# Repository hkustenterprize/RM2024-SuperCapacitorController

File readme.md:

# 香港科技大学ENTERPRIZE战队
# RM2024超级电容控制器
# 硬件方案&软件方案 完全开源

>设计者：蒋益诚 戎羿
> 
>文档撰写：戎羿

## 文件结构

```
Calibration/cal.xlsx                              ----校准用Excel工具表
Core                                              ----核心代码文件
Docs                                              ----文档附图源码
Drivers                                           ----STM32驱动文件
hardware                                          ----硬件项目文件
      --    SuperCap2024_Control_V1.1R_F3_ISOPWR  ----控制板Kicad项目文件
      --    SuperCap2024_Power_V1.2R              ----功率板Kicad项目文件
Middlewares/ST/ARM/DSP/Inc/arm_math.h             ----数学加速库头文件
.clang-format
.clang-tidy
.cproject
CMakeLists.txt                                    ----由CLion生成的CMake编译文件，便于CLion创建项目
CMakeLists_template.txt
Makefile                                          ----由CubeMX生成的MakeFile编译文件
RM2024-SuperCap-F3-V0.2.ioc                       ----STM32CubeMX项目文件
startup_stm32f334x8.s                             ----由CubeMX生成的启动文件
startup_stm32f334x8_SuperCap.s                    ----由CubeMX生成的启动文件改版，当前使用中
STM32F334R8Tx_FLASH.ld                            ----由CubeMX生成的链接文件
STM32F334R8Tx_SuperCap_FLASH.ld                   ----由CubeMX生成的链接文件改版，当前使用中
SuperCap-F3.mk                                    ----队内通用MakeFile库
```

## 使用方法
###	硬件接口&连接

###	软件环境&编译&烧录
本项目基于GCC ARM GNU工具链。
1.	安装GCC环境。以Windows系统下为例，下载MSYS2并安装，在系统环境变量中加入相关目录。
2.	安装`arm-none-eabi-gcc`
      然后即可执行编译操作。需要注意编译时需要指定HARDWARE_ID，否则将会报错。

      `make -j HARDWARE_ID=xxx`

      得到`build/`目录下`RM2024-SuperCap-F3-V1R.elf`文件即为编译成功。

      将elf文件在ozone新建项目中打开，即可通过JLink烧录至MCU中。

## 移植兼容性
该项目通过STM32的HAL库实现大部分去耦，方便移植。

用户代码全部位于 `Core/` 中，将相应文件转移到另生成的项目中可以轻松移植。例如专用STM32G474作为开发用MCU。

而部分相对底层的外设代码，例如HRTIM与ADC的配置等，则需要手动修改。

总体而言该项目可移植性较佳。

## 开源报告
可以见于Github Release处

## 开源说明
本项目通过GPL3.0协议开源

## PCB项目说明
硬件部分使用KiCAD设计。

Github上在线预览：使用[KiCanvas](https://kicanvas.org/)

上板原理图：[预览](https://kicanvas.org/?github=https%3A%2F%2Fgithub.com%2Fhkustenterprize%2FRM2024-SuperCapacitorController%2Fblob%2Fmaster%2Fhardware%2FSuperCap2024_Control_V1.1R_F3_ISOPWR%2FSuperCap2024Control_V1.1R_F3_ISOPWR.kicad_sch)

上板PCB：[预览](https://kicanvas.org/?github=https%3A%2F%2Fgithub.com%2Fhkustenterprize%2FRM2024-SuperCapacitorController%2Fblob%2Fmaster%2Fhardware%2FSuperCap2024_Control_V1.1R_F3_ISOPWR%2FSuperCap2024Control_V1.1R_F3_ISOPWR.kicad_pcb)

下板原理图：[预览](https://kicanvas.org/?github=https%3A%2F%2Fgithub.com%2Fhkustenterprize%2FRM2024-SuperCapacitorController%2Fblob%2Fmaster%2Fhardware%2FSuperCap2024_Power_V1.2R%2FSuperCap2024V1.2R_Power.kicad_sch)

下板PCB：[预览](https://kicanvas.org/?github=https%3A%2F%2Fgithub.com%2Fhkustenterprize%2FRM2024-SuperCapacitorController%2Fblob%2Fmaster%2Fhardware%2FSuperCap2024_Power_V1.2R%2FSuperCap2024V1.2R_Power.kicad_pcb)

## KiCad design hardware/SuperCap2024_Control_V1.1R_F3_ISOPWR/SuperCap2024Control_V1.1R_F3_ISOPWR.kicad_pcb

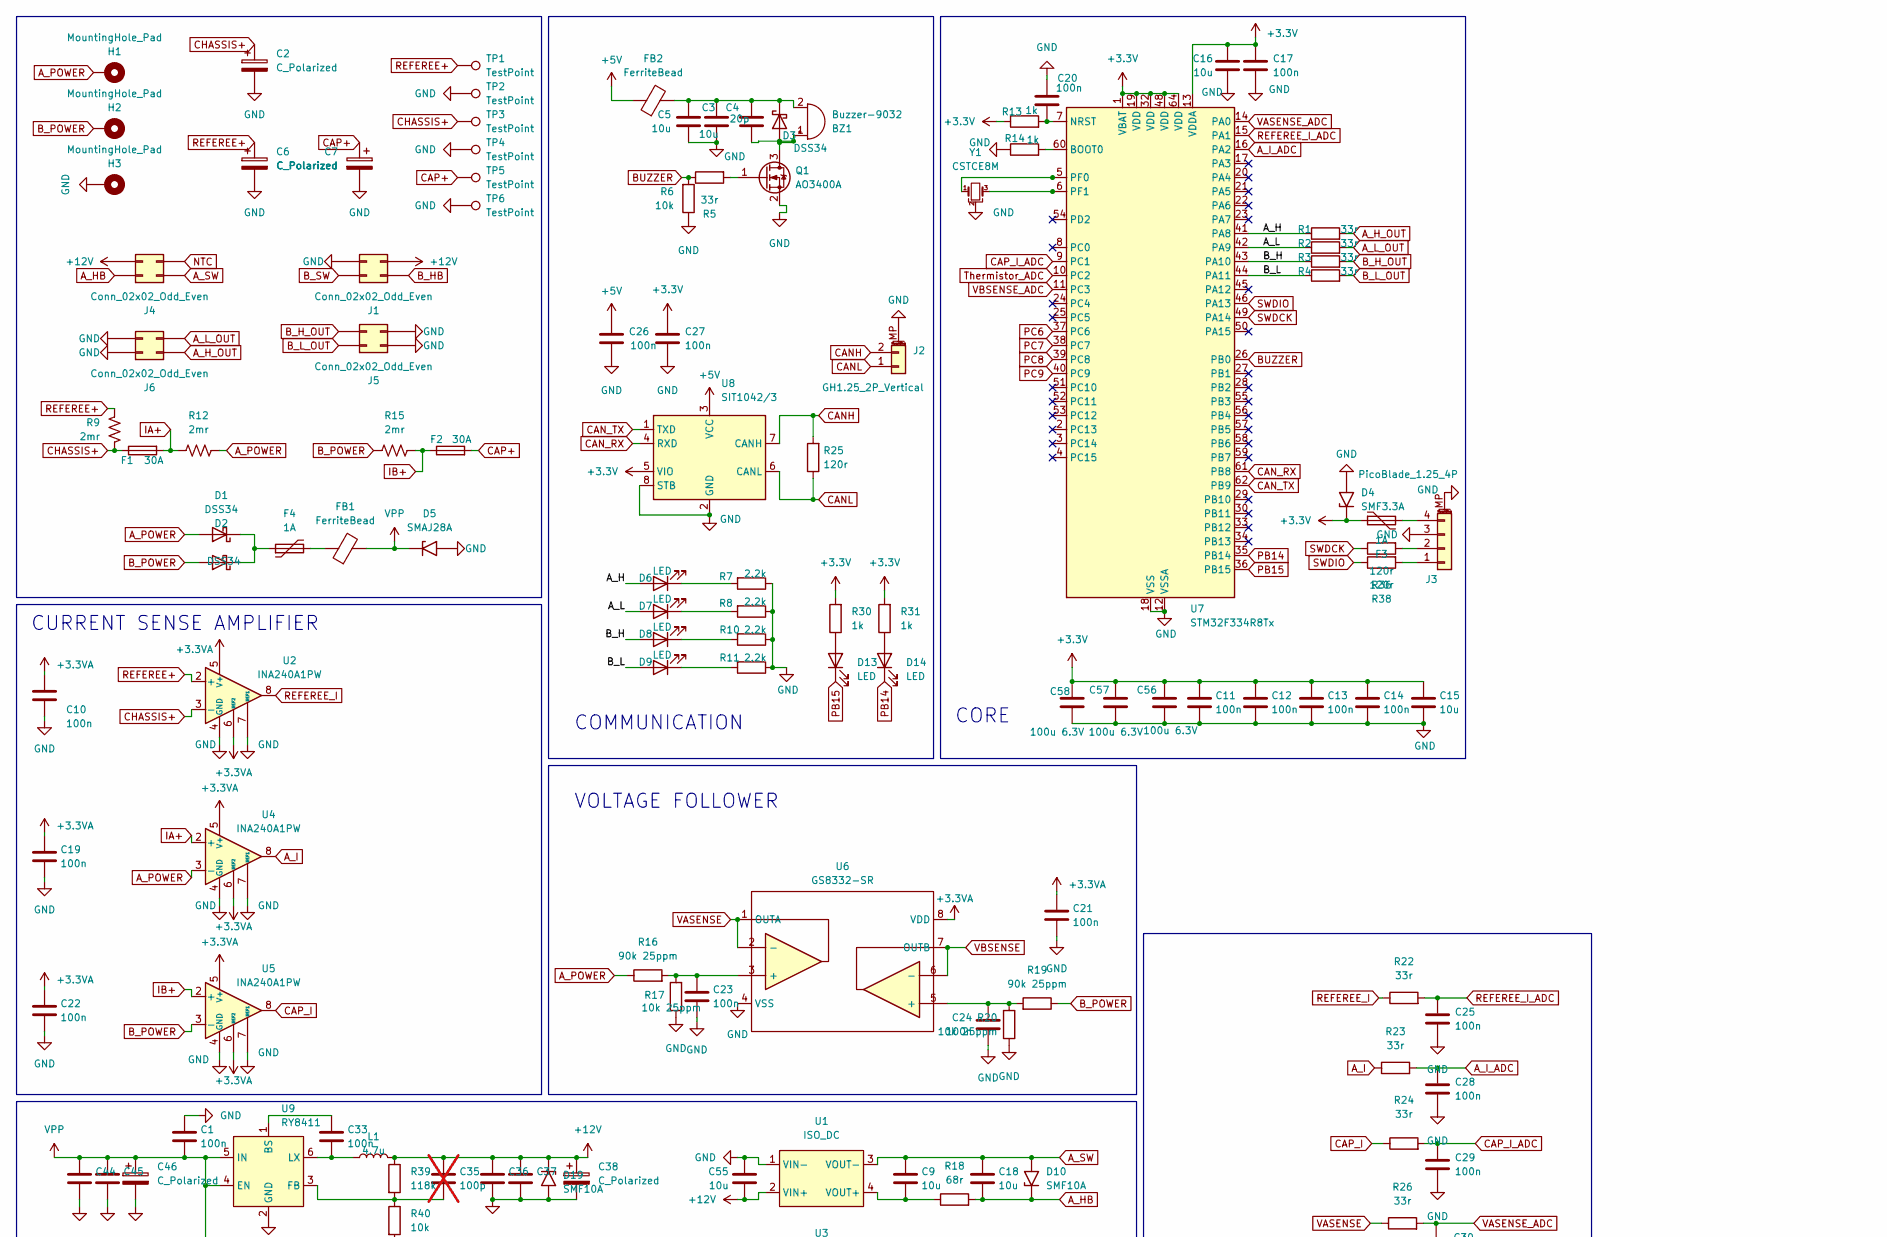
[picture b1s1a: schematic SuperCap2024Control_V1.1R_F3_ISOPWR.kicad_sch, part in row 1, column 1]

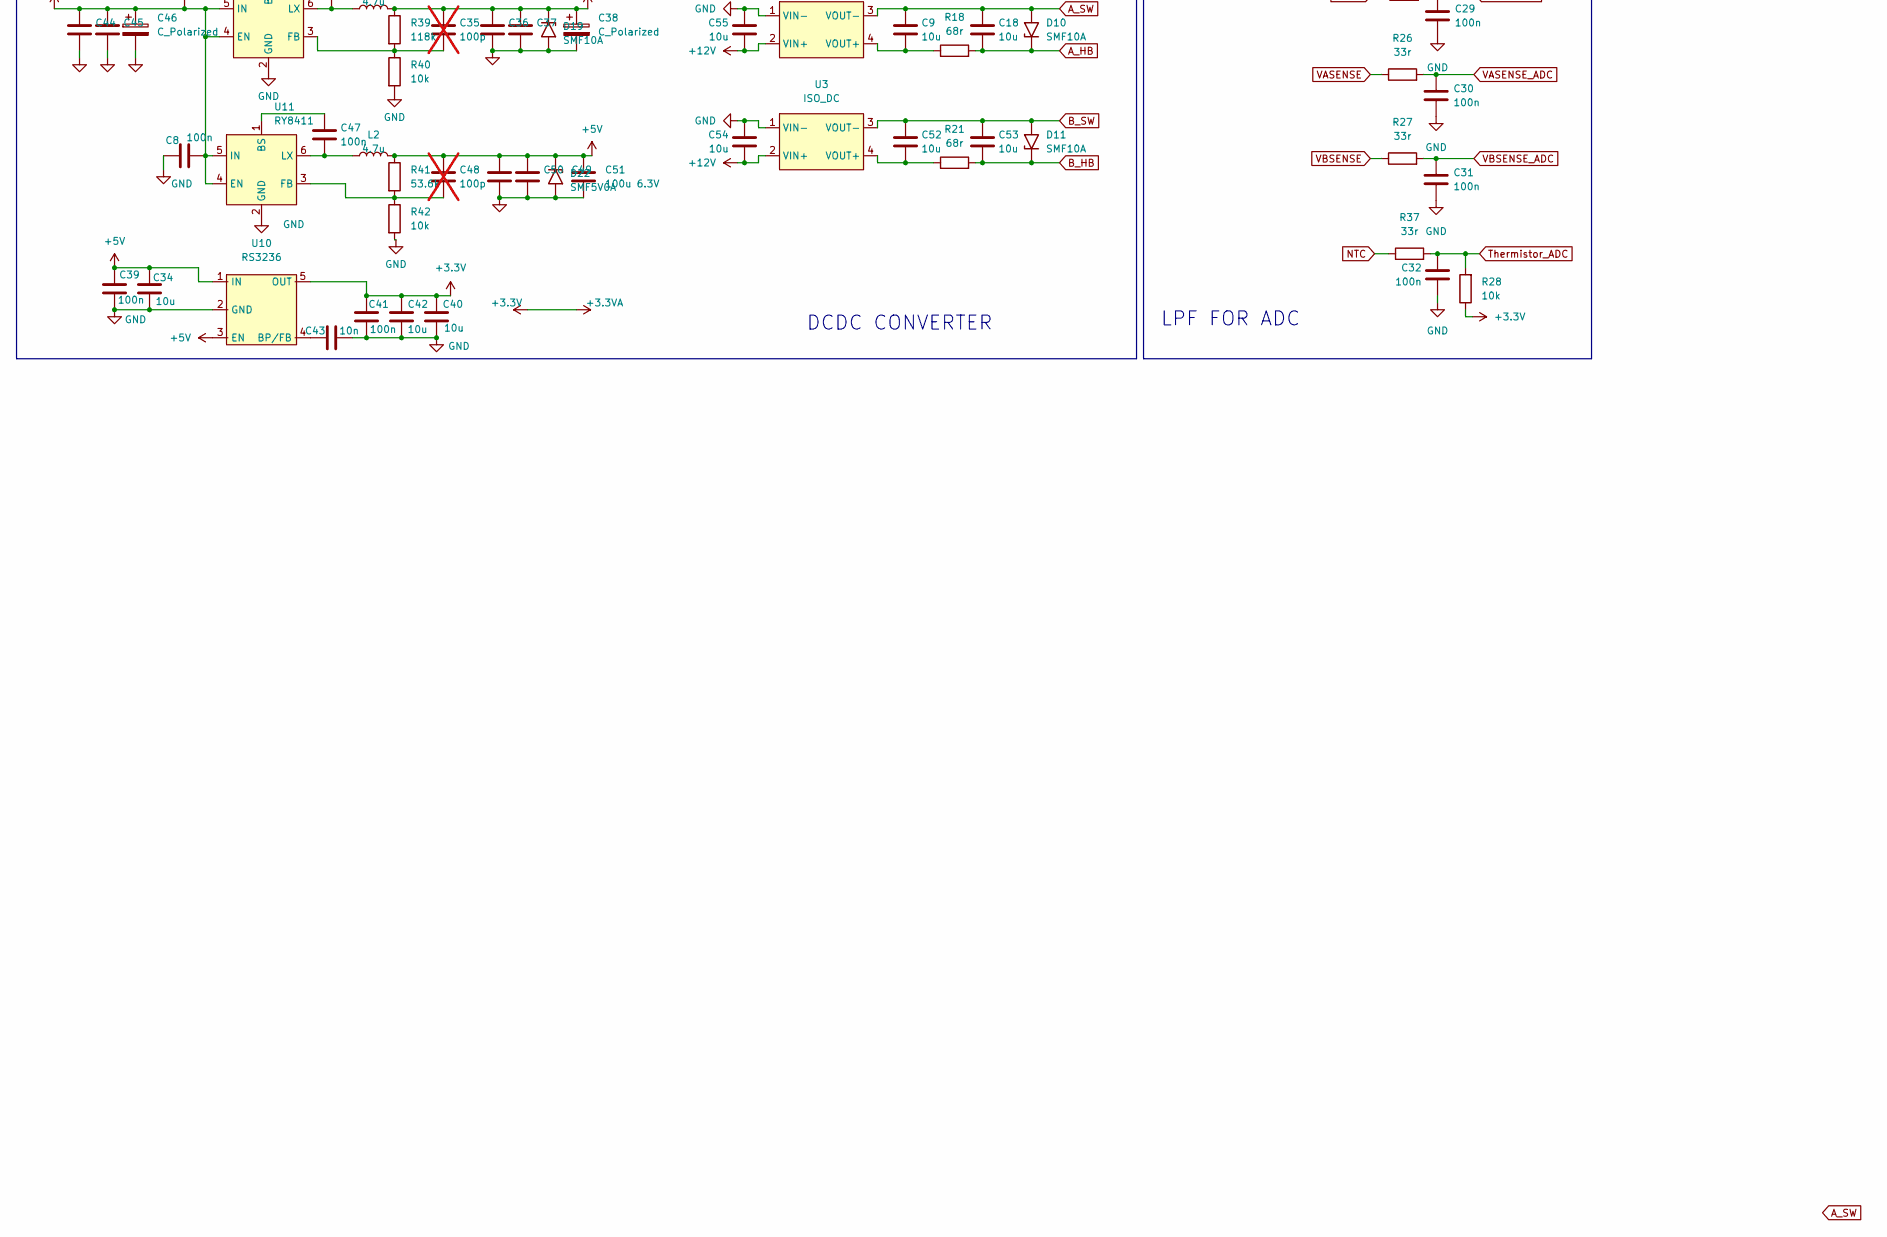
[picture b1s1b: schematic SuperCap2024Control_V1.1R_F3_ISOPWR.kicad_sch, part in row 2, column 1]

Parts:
BZ1: Buzzer-9032; MLT-9032
C1, C8, C10, C11, C12, C13, C14, C17, C19, C20, C21, C22, C23, C24, C25, C26, C27, C28, C29, C30, C31, C32, C33, C39, C41, C47: 100n; C_0603_1608Metric
C2, C6, C7: C_Polarized; CP_Radial_D8.0mm_P3.50mm
C3, C5, C15, C16, C34, C40, C42: 10u; C_0603_1608Metric
C4: 20p; C_0603_1608Metric
C9, C18, C36, C37, C44, C45, C49, C50, C52, C53, C54, C55: 10u; C_1206_3216Metric
C35, C48: 100p; C_0603_1608Metric; not fitted
C38, C46: C_Polarized; CP_EIA-6032-28_Kemet-C
C43: 10n; C_0603_1608Metric
C51, C56, C57, C58: 100u 6.3V; C_1206_3216Metric
D1, D2, D3: DSS34; D_SMF
D4: SMF3.3A; D_SMF
D5: SMAJ28A; D_SMA
D6, D7, D8, D9, D13, D14: LED; LED_0603_1608Metric
D10, D11, D19: SMF10A; D_SMF
D22: SMF5V0A; D_SMF
F1, F2: 30A; Fuse_1206_3216Metric
F3, F4: 1A; Fuse_1206_3216Metric
FB1: FerriteBead; L_1206_3216Metric
FB2: FerriteBead; L_0603_1608Metric
H1, H2, H3: MountingHole_Pad; MountingHole_3.2mm_M3_ISO14580_Pad
J1, J4: Conn_02x02_Odd_Even; PinHeader_2x02_P2.54mm_Vertical_SMD
J2: GH1.25_2P_Vertical; JST_GH_SM02B-GHS-TB_1x02-1MP_P1.25mm_Horizontal
J3: PicoBlade_1.25_4P; Molex_PicoBlade_53261-0471_1x04-1MP_P1.25mm_Horizontal
J5, J6: Conn_02x02_Odd_Even; PinHeader_2x02_P2.54mm_Vertical
L1: 4.7u; L_Bourns-SRN4018
L2: 4.7u; L_Sunlord_SWPA252012S
Q1: AO3400A; SOT-23
R1, R2, R3, R4, R5, R22, R23, R24, R26, R27, R37: 33r; R_0603_1608Metric
R6, R28, R40, R42: 10k; R_0603_1608Metric
R7, R8, R10, R11: 2.2k; R_0603_1608Metric
R9, R12, R15: 2mr; R_2512_6332Metric
R13, R14, R30, R31: 1k; R_0603_1608Metric
R16, R19: 90k 25ppm; R_0603_1608Metric
R17, R20: 10k 25ppm; R_0603_1608Metric
R18, R21: 68r; R_0603_1608Metric
R25, R36, R38: 120r; R_0603_1608Metric
R39: 118k; R_0603_1608Metric
R41: 53.6k; R_0603_1608Metric
TP1, TP2, TP3, TP4, TP5, TP6: TestPoint; TestPoint_Plated_Hole_D3.0mm
U1, U3: ISO_DC; BxxxxS-1W
U2, U4, U5: INA240A1PW; TSSOP-8_4.4x3mm_P0.65mm
U6: GS8332-SR; SOIC-8_3.9x4.9mm_P1.27mm
U7: STM32F334R8Tx; LQFP-64_10x10mm_P0.5mm
U8: SIT1042/3; SOIC-8_3.9x4.9mm_P1.27mm
U9, U11: RY8411; SOT-23-6
U10: RS3236; SOT-23-5
Y1: CSTCE8M; Resonator_SMD_Murata_CSTxExxV-3Pin_3.0x1.1mm

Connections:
+3.3V: C10.1, C11.1, C12.1, C13.1, C14.1, C15.1, C16.2, C17.2, C19.1, C21.1, C22.1, C27.2, C40.1, C41.1, C42.1, C56.1, C57.1, C58.1, D4.1 (A1), F3.1, R13.1, R28.1, R30.2, R31.2, U2.5 (V+), U2.6 (REF2), U4.5 (V+), U4.6 (REF2), U5.5 (V+), U5.6 (REF2), U6.8 (VDD), U7.1 (VBAT), U7.13 (VDDA), U7.19 (VDD), U7.32 (VDD), U7.48 (VDD), U7.64 (VDD), U8.5 (VIO), U10.5 (OUT)
+5V: C26.2, C34.1, C39.1, C48.1, C49.1, C50.1, C51.1, D22.1 (A1), FB2.1, L2.2, R41.1, U8.3 (VCC), U10.1 (IN), U10.3 (EN)
+12V: C35.1, C36.1, C37.1, C38.1, C54.2, C55.2, D19.1 (A1), J1.4, J4.3, L1.2, R39.1, U1.2 (VIN+), U3.2 (VIN+)
/A_H: D6.2 (A), R1.1, U7.41 (PA8)
/A_L: D7.2 (A), R2.1, U7.42 (PA9)
/B_H: D8.2 (A), R3.1, U7.43 (PA10)
/B_L: D9.2 (A), R4.1, U7.44 (PA11)
A_HB: C18.2, D10.1 (A1), J4.1, R18.2
A_H_OUT: J6.2, R1.2
A_I: R23.1, U4.8
A_I_ADC: C28.2, R23.2, U7.16 (PA2)
A_L_OUT: J6.4, R2.2
A_POWER: D1.2 (A), H1.1, R12.2, R16.1, U4.3 (-)
A_SW: C9.1, C18.1, D10.2 (A2), J4.2, U1.3 (VOUT-)
BUZZER: R5.1, R6.2, U7.26 (PB0)
B_HB: C53.2, D11.1 (A1), J1.2, R21.2
B_H_OUT: J5.3, R3.2
B_L_OUT: J5.1, R4.2
B_POWER: D2.2 (A), H2.1, R15.1, R19.1, U5.3 (-)
B_SW: C52.1, C53.1, D11.2 (A2), J1.1, U3.3 (VOUT-)
CANH: J2.2, R25.2, U8.7 (CANH)
CANL: J2.1, R25.1, U8.6 (CANL)
CAN_RX: U7.61 (PB8), U8.4 (RXD)
CAN_TX: U7.62 (PB9), U8.1 (TXD)
CAP+: C7.1, F2.2, TP5.1
CAP_I: R24.1, U5.8
CAP_I_ADC: C29.2, R24.2, U7.9 (PC1)
CHASSIS+: C2.1, F1.1, R9.2, TP3.1, U2.3 (-)
GND: C1.1, C2.2, C3.1, C5.1, C6.2, C7.2, C8.2, C10.2, C11.2, C12.2, C13.2, C14.2, C15.2, C16.1, C17.1, C19.2, C20.2, C21.2, C22.2, C23.2, C24.2, C25.1, C26.1, C27.1, C28.1, C29.1, C30.1, C31.1, C32.2, C34.2, C36.2, C37.2, C38.2, C39.2, C40.2, C41.2, C42.2, C43.2, C44.2, C45.2, C46.2, C49.2, C50.2, C51.2, C54.1, C55.1, C56.2, C57.2, C58.2, D4.2 (A2), D5.2 (A2), D19.2 (A2), D22.2 (A2), H3.1, J1.3, J2.MP (MountPin), J3.3, J3.MP (MountPin), J5.2, J5.4, J6.1, J6.3, Q1.2 (S), R6.1, R7.1, R8.1, R10.1, R11.1, R14.1, R17.1, R20.1, R40.2, R42.2, TP2.1, TP4.1, TP6.1, U1.1 (VIN-), U2.1 (GND), U2.4 (GND), U2.7 (REF1), U3.1 (VIN-), U4.1 (GND), U4.4 (GND), U4.7 (REF1), U5.1 (GND), U5.4 (GND), U5.7 (REF1), U6.4 (VSS), U7.12 (VSSA), U7.18 (VSS), U7.31 (VSS), U7.47 (VSS), U7.63 (VSS), U8.2 (GND), U8.8 (STB), U9.2 (GND), U10.2 (GND), U11.2 (GND), Y1.2
IA+: F1.2, R12.1, U4.2 (+)
IB+: F2.1, R15.2, U5.2 (+)
NTC: J4.4, R37.1
unnamed: BZ1.2 (+), C3.2, C4.2, C5.2, D3.1 (K), FB2.2
unnamed: BZ1.1 (-), C4.1, D3.2 (A), Q1.3 (D)
unnamed: C23.1, R16.2, R17.2, U6.3 (+)
unnamed: C24.1, R19.2, R20.2, U6.5 (+)
unnamed: D1.1 (K), D2.1 (K), F4.1
unnamed: D6.1 (K), R7.2
unnamed: D7.1 (K), R8.2
unnamed: D8.1 (K), R10.2
unnamed: D9.1 (K), R11.2
unnamed: D13.2 (A), R30.1
unnamed: D14.2 (A), R31.1
unnamed: F4.2, FB1.1
unnamed: J3.1, R38.2
unnamed: J3.2, R36.2
unnamed: F3.2, J3.4
unnamed: Q1.1 (G), R5.2
unnamed: C9.2, R18.1, U1.4 (VOUT+)
unnamed: C52.2, R21.1, U3.4 (VOUT+)
unnamed: R14.2, U7.60 (BOOT0)
unnamed: C20.1, R13.2, U7.7 (NRST)
unnamed: U7.5 (PF0), Y1.1
unnamed: U7.6 (PF1), Y1.3
unnamed: C33.1, U9.1 (BS)
unnamed: C35.2, R39.2, R40.1, U9.3 (FB)
unnamed: C33.2, L1.1, U9.6 (LX)
unnamed: C43.1, U10.4 (BP/FB)
unnamed: C47.1, U11.1 (BS)
unnamed: C48.2, R41.2, R42.1, U11.3 (FB)
unnamed: C47.2, L2.1, U11.6 (LX)
PB14: D14.1 (K), U7.35 (PB14)
PB15: D13.1 (K), U7.36 (PB15)
PC6: U7.37 (PC6)
PC7: U7.38 (PC7)
PC8: U7.39 (PC8)
PC9: U7.40 (PC9)
REFEREE+: C6.1, R9.1, TP1.1, U2.2 (+)
REFEREE_I: R22.1, U2.8
REFEREE_I_ADC: C25.2, R22.2, U7.15 (PA1)
SWDCK: R36.1, U7.49 (PA14)
SWDIO: R38.1, U7.46 (PA13)
Thermistor_ADC: C32.1, R28.2, R37.2, U7.10 (PC2)
VASENSE: R26.1, U6.1 (OUTA), U6.2 (-)
VASENSE_ADC: C30.2, R26.2, U7.14 (PA0)
VBSENSE: R27.1, U6.6 (-), U6.7 (OUTB)
VBSENSE_ADC: C31.2, R27.2, U7.11 (PC3)
VPP: C1.2, C8.1, C44.1, C45.1, C46.1, D5.1 (A1), FB1.2, U9.4 (EN), U9.5 (IN), U11.4 (EN), U11.5 (IN)

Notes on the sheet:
COMMUNICATION
CURRENT SENSE AMPLIFIER
CORE
DCDC CONVERTER
VOLTAGE FOLLOWER
LPF FOR ADC

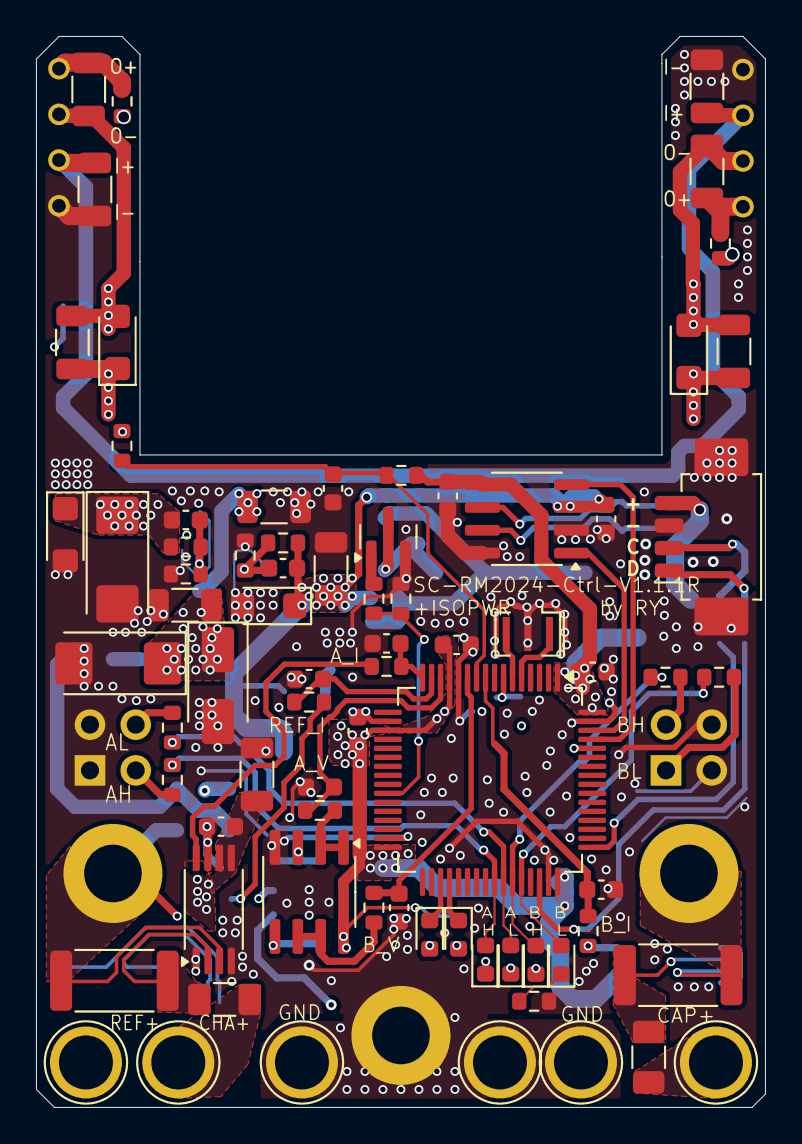
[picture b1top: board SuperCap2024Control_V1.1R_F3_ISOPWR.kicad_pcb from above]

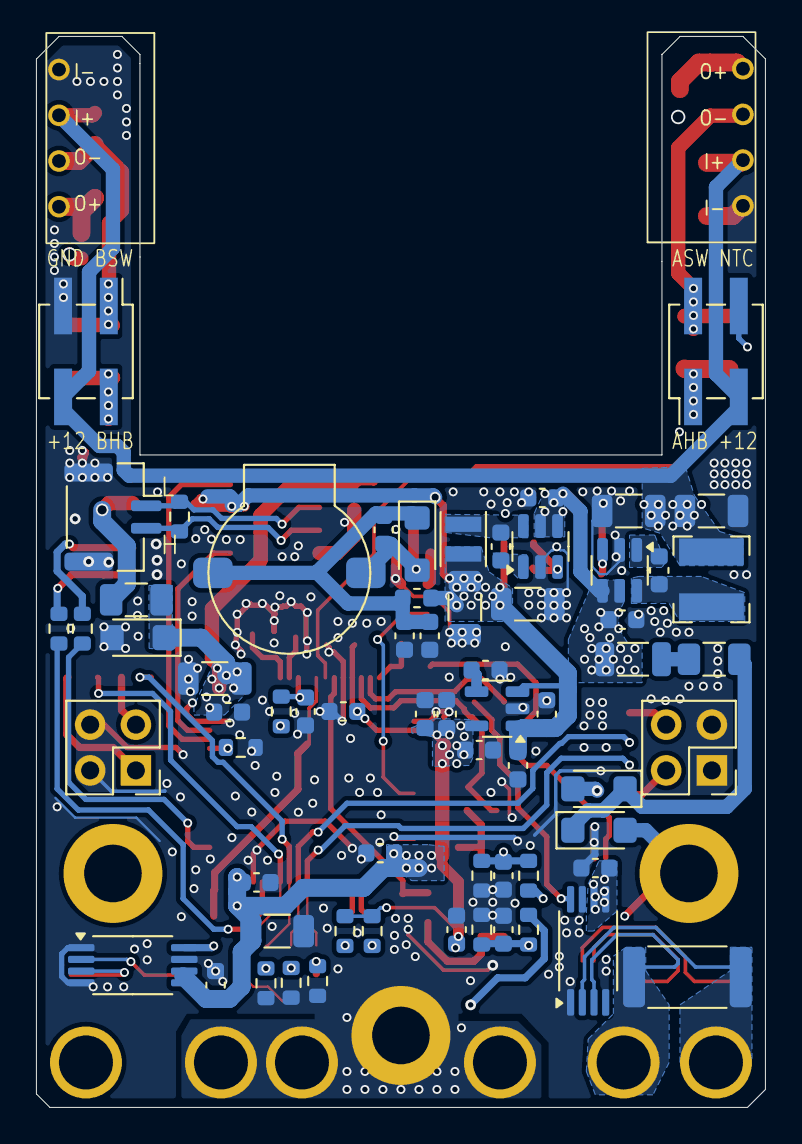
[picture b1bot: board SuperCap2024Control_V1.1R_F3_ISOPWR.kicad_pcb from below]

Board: 4 copper layers, 40.5 x 59.5 mm, 144 parts (67 on the bottom side), 74 nets.

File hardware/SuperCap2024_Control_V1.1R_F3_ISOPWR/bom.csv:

Designator,Footprint,Quantity,Value,LCSC Part #
BZ1,MLT-9032,1,Buzzer-9032,
"C1, C10, C11, C12, C13, C14, C17, C19, C20, C21, C22, C23, C24, C25, C26, C27, C28, C29, C30, C31, C32, C33, C39, C41, C47, C8",0603,26,100n,
"C15, C16, C3, C34, C40, C42, C5",0603,7,10u,
"C18, C36, C37, C44, C45, C49, C50, C52, C53, C54, C55, C9",1206,12,10u,
"C38, C46",CP_EIA-6032-28_Kemet-C,2,C_Polarized,
C4,0603,1,20p,
C43,0603,1,10n,
"C51, C56, C57, C58",1206,4,100u 6.3V,
"D1, D2, D3",D_SMF,3,DSS34,
"D10, D11, D19",D_SMF,3,SMF10A,
"D13, D14, D6, D7, D8, D9",0603,6,LED,
D22,D_SMF,1,SMF5V0A,
D4,D_SMF,1,SMF3.3A,
D5,D_SMA,1,SMAJ28A,
"F1, F2",1206,2,30A,
"F3, F4",1206,2,1A,
FB1,1206,1,FerriteBead,
FB2,0603,1,FerriteBead,
"H1, H2, H3",MountingHole_3.2mm_M3_ISO14580_Pad,3,MountingHole_Pad,
"J1, J4",PinHeader_2x02_P2.54mm_Vertical_SMD,2,Conn_02x02_Odd_Even,
J2,JST_GH_SM02B-GHS-TB_1x02-1MP_P1.25mm_Horizontal,1,Conn_01x02_MountingPin,
J3,Molex_PicoBlade_53261-0471_1x04-1MP_P1.25mm_Horizontal,1,Conn_01x04_MountingPin,
"J5, J6",PinHeader_2x02_P2.54mm_Vertical,2,Conn_02x02_Odd_Even,
L1,L_Bourns-SRN4018,1,4.7u,
L2,L_Sunlord_SWPA252012S,1,4.7u,
Q1,SOT-23,1,AO3400A,
"R1, R2, R22, R23, R24, R26, R27, R3, R37, R4, R5",0603,11,33r,
"R10, R11, R7, R8",0603,4,2.2k,
"R12, R15, R9",2512,3,2mr,
"R13, R14, R30, R31",0603,4,1k,
"R16, R19",0603,2,90k 25ppm,
"R17, R20",0603,2,10k 25ppm,
"R18, R21",0603,2,68r,
"R25, R36, R38",0603,3,120r,
"R28, R40, R42, R6",0603,4,10k,
R39,0603,1,118k,
R41,0603,1,53.6k,
"TP1, TP2, TP3, TP4, TP5, TP6",TestPoint_Plated_Hole_D3.0mm,6,TestPoint,
"U1, U3",BxxxxS-1W,2,ISO_DC,
U10,SOT-23-5,1,RS3236,
"U11, U9",SOT-23-6,2,RY8411,
"U2, U4, U5",TSSOP-8_4.4x3mm_P0.65mm,3,INA240A1PW,
U6,SOIC-8_3.9x4.9mm_P1.27mm,1,GS8332-SR,
U7,LQFP-64_10x10mm_P0.5mm,1,STM32F334R8Tx,
U8,SOIC-8_3.9x4.9mm_P1.27mm,1,SIT1042/3,
Y1,Resonator_SMD_Murata_CSTxExxV-3Pin_3.0x1.1mm,1,CSTCE8M,

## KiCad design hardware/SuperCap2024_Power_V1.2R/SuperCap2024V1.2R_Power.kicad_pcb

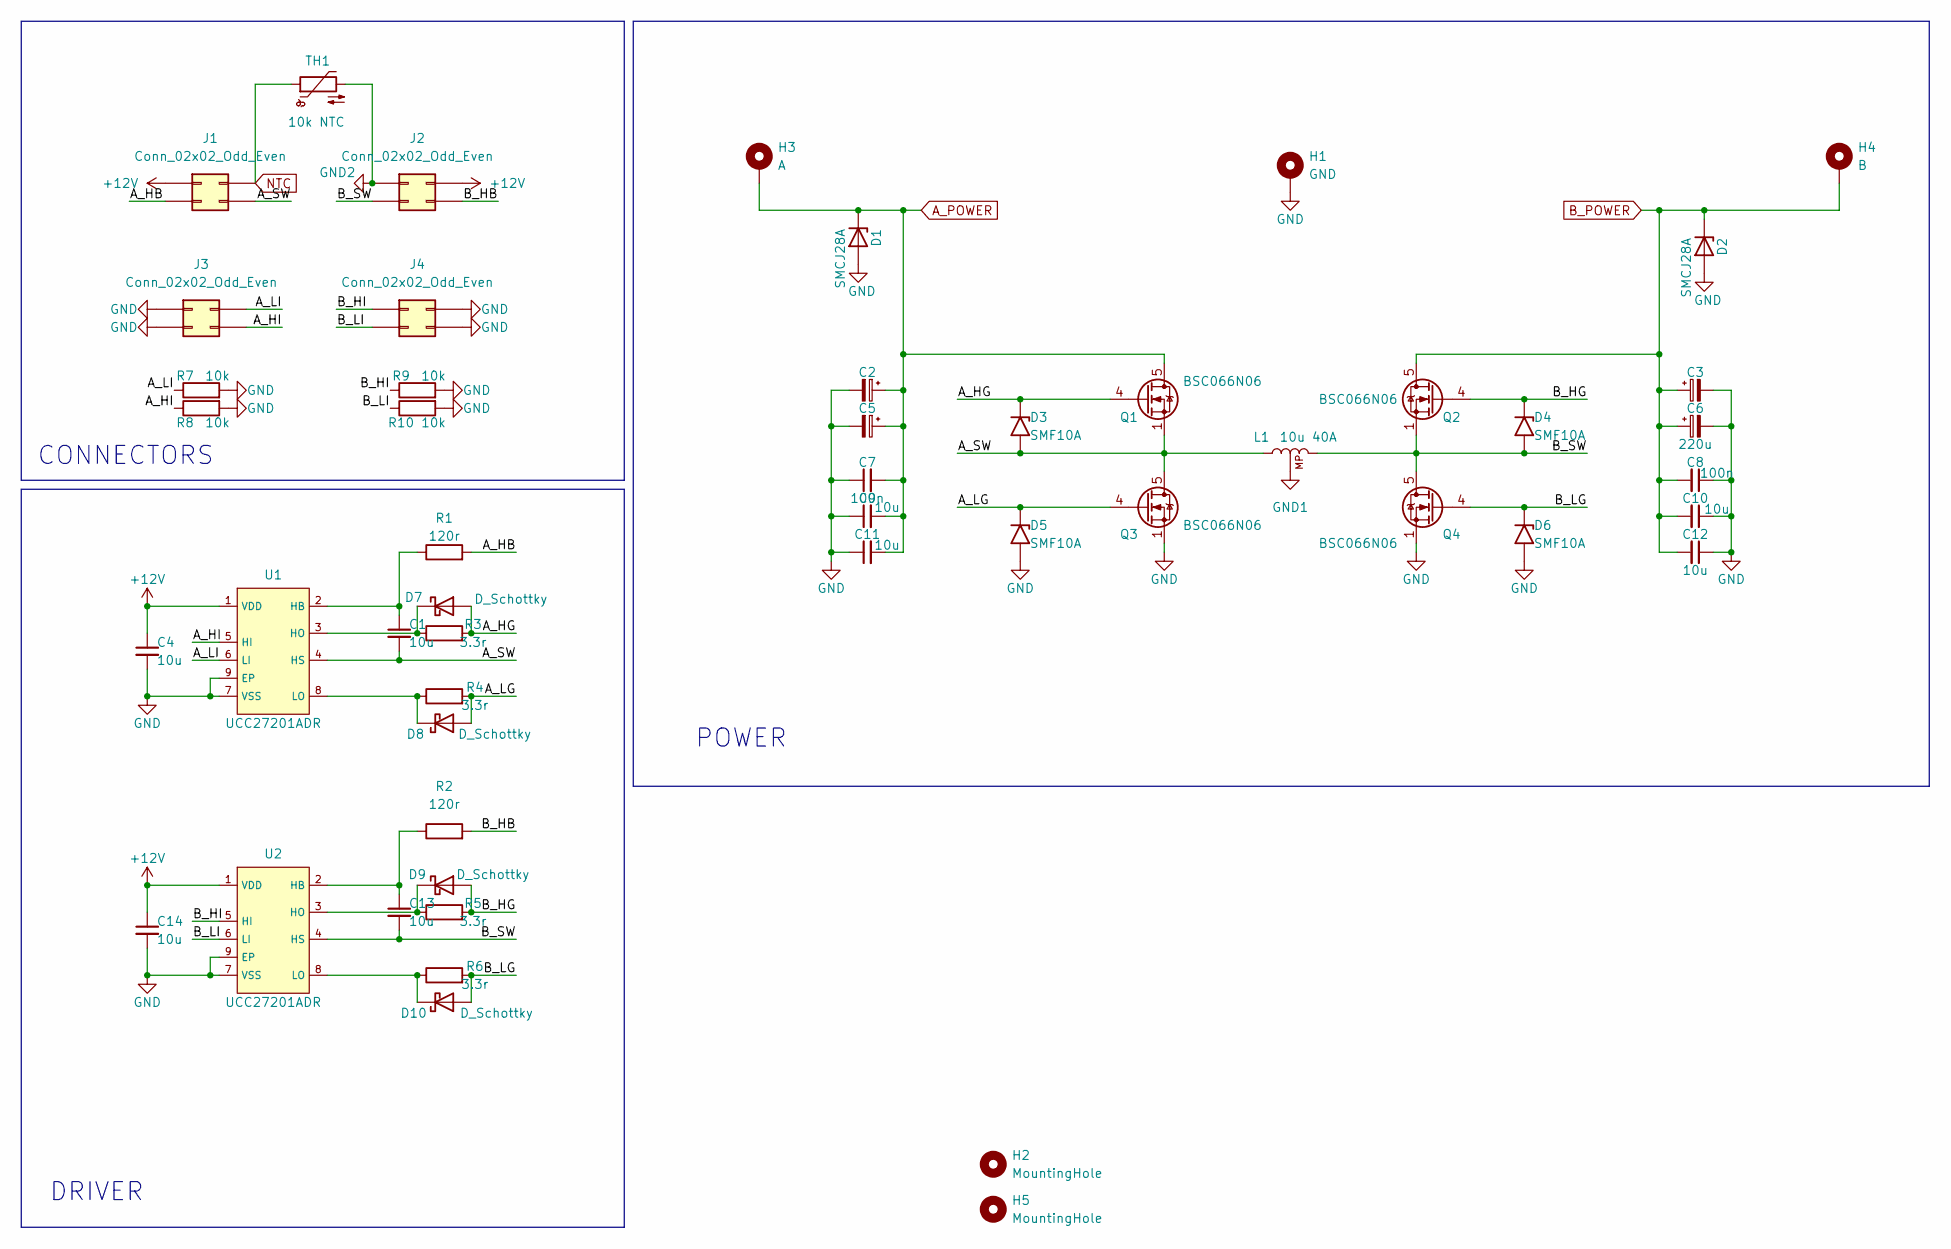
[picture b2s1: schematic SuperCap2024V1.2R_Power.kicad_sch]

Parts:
C1, C13: 10u; C_0603_1608Metric
C2, C3, C5, C6: 220u; CP_Elec_8x10
C4, C9, C10, C11, C12, C14: 10u; C_1206_3216Metric
C7, C8: 100n; C_0603_1608Metric
D1, D2: SMCJ28A; D_SMC
D3, D4, D5, D6: SMF10A; D_SOD-123F
D7, D8, D9, D10: D_Schottky; D_SOD-123F
H1: GND; TestPoint_Pad_D4.0mm
H2, H5: MountingHole; MountingHole_3.2mm_M3
H3: A; TestPoint_Pad_D4.0mm
H4: B; TestPoint_Pad_D4.0mm
J1, J2, J3, J4: Conn_02x02_Odd_Even; PinHeader_2x02_P2.54mm_Vertical_SMD
L1: 10u 40A; PQ2617BHA
Q1, Q2, Q3, Q4: BSC066N06; TDSON-8-1_HandSolder
R1, R2: 120r; R_1206_3216Metric
R3, R4, R5, R6: 3.3r; R_0603_1608Metric
R7, R8, R9, R10: 10k; R_0603_1608Metric
TH1: 10k NTC; R_1206_3216Metric
U1, U2: UCC27201ADR; SOP-8_3.9x4.9mm_P1.27mm

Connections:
+12V: C4.1, C14.1, J1.1, J2.2, U1.1 (VDD), U2.1 (VDD)
/A_HB: J1.3, R1.2
/A_HG: D3.1 (A1), D7.2 (A), Q1.4 (G), R3.2
/A_HI: J3.4, R8.1, U1.5 (HI)
/A_LG: D5.1 (A1), D8.2 (A), Q3.4 (G), R4.2
/A_LI: J3.2, R7.1, U1.6 (LI)
/A_SW: C1.2, D3.2 (A2), J1.4, L1.1, Q1.1 (S), Q1.2 (S), Q1.3 (S), Q3.5 (D), U1.4 (HS)
/B_HB: J2.4, R2.2
/B_HG: D4.1 (A1), D9.2 (A), Q2.4 (G), R5.2
/B_HI: J4.1, R9.1, U2.5 (HI)
/B_LG: D6.1 (A1), D10.2 (A), Q4.4 (G), R6.2
/B_LI: J4.3, R10.1, U2.6 (LI)
/B_SW: C13.2, D4.2 (A2), J2.3, L1.2, Q2.1 (S), Q2.2 (S), Q2.3 (S), Q4.5 (D), U2.4 (HS)
A_POWER: C2.1, C5.1, C7.2, C9.2, C11.2, D1.1 (K), H3.1, Q1.5 (D)
B_POWER: C3.1, C6.1, C8.2, C10.2, C12.2, D2.1 (K), H4.1, Q2.5 (D)
GND: C2.2, C3.2, C4.2, C5.2, C6.2, C7.1, C8.1, C9.1, C10.1, C11.1, C12.1, C14.2, D1.2 (A), D2.2 (A), D5.2 (A2), D6.2 (A2), H1.1, J3.1, J3.3, J4.2, J4.4, Q3.1 (S), Q3.2 (S), Q3.3 (S), Q4.1 (S), Q4.2 (S), Q4.3 (S), R7.2, R8.2, R9.2, R10.2, U1.7 (VSS), U1.9 (EP), U2.7 (VSS), U2.9 (EP)
GND1: L1.3 (MP)
GND2: J2.1, TH1.2
NTC: J1.2, TH1.1
unnamed: C1.1, R1.1, U1.2 (HB)
unnamed: D7.1 (K), R3.1, U1.3 (HO)
unnamed: D8.1 (K), R4.1, U1.8 (LO)
unnamed: C13.1, R2.1, U2.2 (HB)
unnamed: D9.1 (K), R5.1, U2.3 (HO)
unnamed: D10.1 (K), R6.1, U2.8 (LO)

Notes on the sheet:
POWER
DRIVER
CONNECTORS

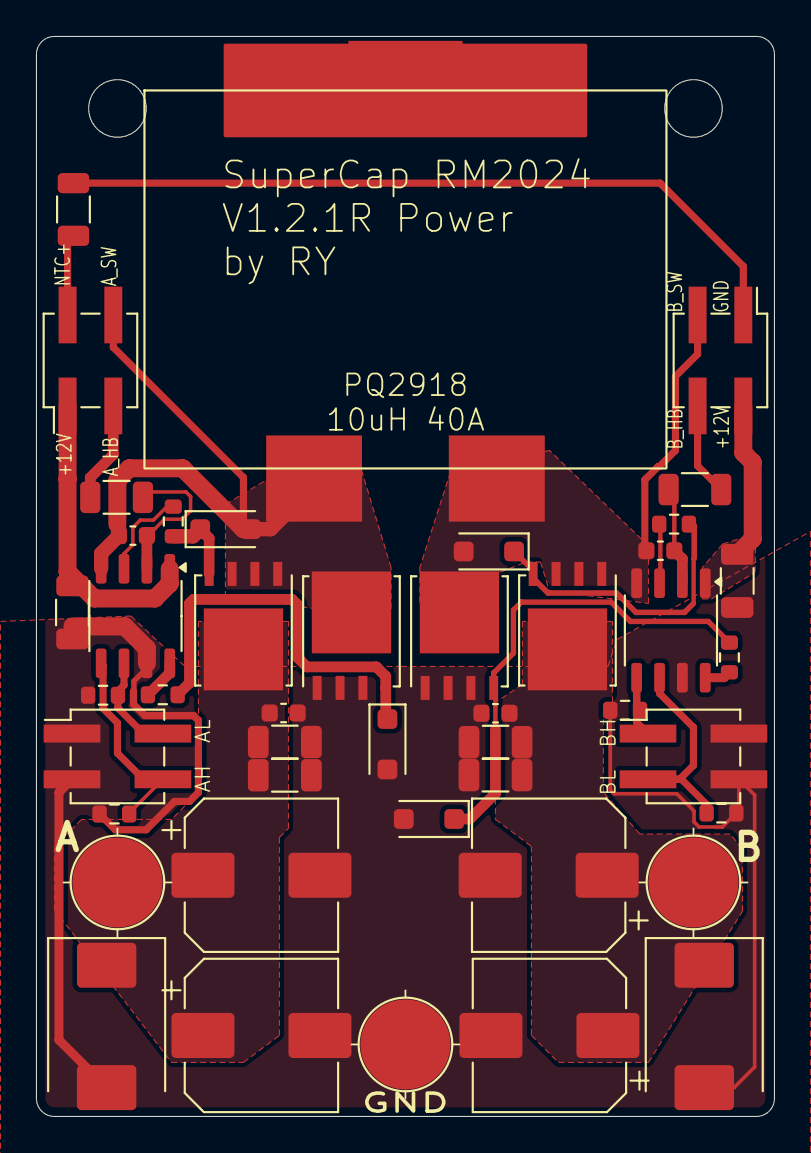
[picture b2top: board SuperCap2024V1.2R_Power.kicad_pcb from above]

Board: 2 copper layers, 41.0 x 60.0 mm, 47 parts (0 on the bottom side), 24 nets.

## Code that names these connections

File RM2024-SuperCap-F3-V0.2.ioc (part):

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Mcu.Name=STM32F334R(6-8)Tx
Mcu.Package=LQFP64
Mcu.UserName=STM32F334R8Tx
PA0.GPIOParameters=GPIO_Label
PA0.GPIO_Label=V_SENSE_A
PA0.Mode=IN1-Single-Ended
PA0.Signal=ADC1_IN1
PA1.GPIOParameters=GPIO_Label
PA1.GPIO_Label=I_SENSE_JUDGE
PA1.Mode=IN2-Single-Ended
PA1.Signal=ADC1_IN2
PA10.GPIOParameters=GPIO_Label
PA10.GPIO_Label=MOS_B_H
PA10.Mode=Output_TB1TB2
PA10.Signal=HRTIM1_CHB1
PA11.GPIOParameters=GPIO_Label
PA11.GPIO_Label=MOS_B_L
PA11.Mode=Output_TB1TB2
PA11.Signal=HRTIM1_CHB2
PA13.Mode=Serial_Wire
PA13.Signal=SYS_JTMS-SWDIO
PA14.Mode=Serial_Wire
PA14.Signal=SYS_JTCK-SWCLK
PA2.GPIOParameters=GPIO_Label
PA2.GPIO_Label=I_SENSE_A
PA2.Mode=IN3-Single-Ended
PA2.Signal=ADC1_IN3
PA8.GPIOParameters=GPIO_Label
PA8.GPIO_Label=MOS_A_H
PA8.Mode=Output_TA1TA2
PA8.Signal=HRTIM1_CHA1
PA9.GPIOParameters=GPIO_Label
PA9.GPIO_Label=MOS_A_L
PA9.Mode=Output_TA1TA2
PA9.Signal=HRTIM1_CHA2
PB0.GPIOParameters=GPIO_Label
PB0.GPIO_Label=TIM1_CH2N_BUZZER
PB0.Mode=PWM Generation2 CH2N
PB0.Signal=TIM1_CH2N
PB14.GPIOParameters=GPIO_PuPd,GPIO_ModeDefaultOutputPP
PB14.GPIO_ModeDefaultOutputPP=GPIO_MODE_OUTPUT_OD
PB14.GPIO_PuPd=GPIO_NOPULL
PB14.Signal=GPIO_Output
PB15.GPIOParameters=GPIO_PuPd,GPIO_ModeDefaultOutputPP
PB15.GPIO_ModeDefaultOutputPP=GPIO_MODE_OUTPUT_OD
PB15.GPIO_PuPd=GPIO_NOPULL
PB15.Signal=GPIO_Output
PB3.Mode=Asynchronous
PB3.Signal=USART2_TX
PB4.Mode=Asynchronous
PB4.Signal=USART2_RX
PB8.Mode=CAN_Activate
PB8.Signal=CAN_RX
PB9.Mode=CAN_Activate
PB9.Signal=CAN_TX
PC1.GPIOParameters=GPIO_Label
PC1.GPIO_Label=I_SENSE_CAP
PC1.Signal=ADCx_IN7
PC2.GPIOParameters=GPIO_Label
PC2.GPIO_Label=SENSE_THERMAL
PC2.Signal=ADCx_IN8
PC3.GPIOParameters=GPIO_Label
PC3.GPIO_Label=V_SENSE_B
PC3.Signal=ADCx_IN9
PF0\ /\ OSC_IN.Mode=HSE-External-Oscillator
PF0\ /\ OSC_IN.Signal=RCC_OSC_IN
PF1\ /\ OSC_OUT.Mode=HSE-External-Oscillator
PF1\ /\ OSC_OUT.Signal=RCC_OSC_OUT
RCC.HSEPLLFreq_Value=8000000
RCC.HSE_VALUE=8000000
RCC.SYSCLKFreq_VALUE=72000000
RCC.SYSCLKSourceVirtual=RCC_SYSCLKSOURCE_PLLCLK
board=custom

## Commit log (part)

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2024-09-21 Git History Cleared: Init
2024-09-22 Add PCB preview in readme.md
2024-10-08 Disable -ffreestanding Flag in Makefile so that Newer Version will not have error
2024-11-09 Fix on incorrect reference to processedSampleData in CALIBRATION_MODE
